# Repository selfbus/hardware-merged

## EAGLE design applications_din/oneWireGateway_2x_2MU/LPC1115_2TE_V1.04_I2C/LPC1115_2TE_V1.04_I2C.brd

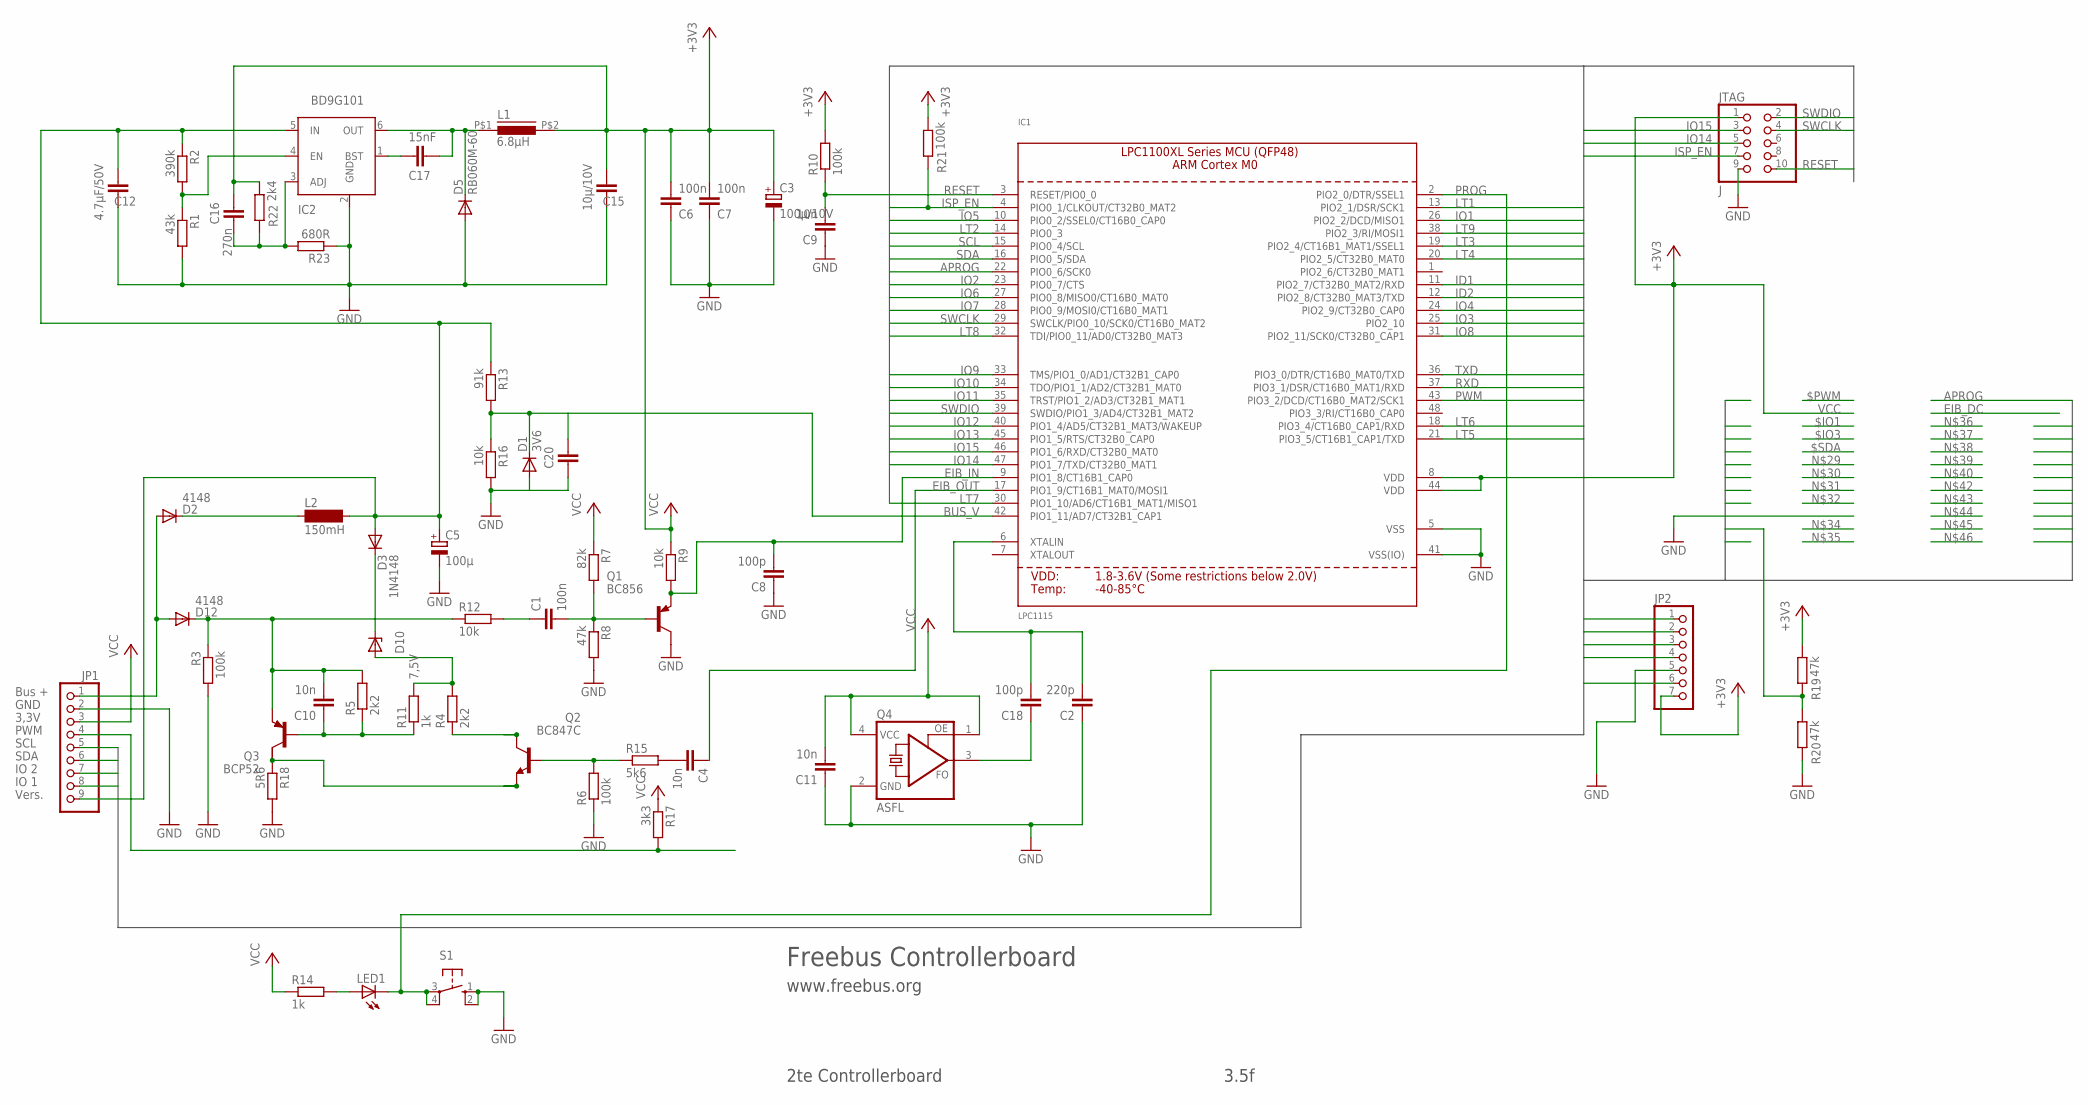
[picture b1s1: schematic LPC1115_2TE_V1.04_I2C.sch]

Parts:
C1, C6, C7: 100n; C1206
C2: 220p; C1206
C3: 100µ/10V; E2,5-5
C4, C10, C11: 10n; C1206
C5: 100µ; E3,5-8
C8: 100p; C1206K
C9: 10n; C1206K
C12: 4.7µF/50V; C1206K
C15: 10µ/10V; C1206K
C16: 270n; C1206
C17: 15nF; C1206
C18: 100p; C1206
C20: C-EUC1206; C1206
D1: 3V6; MINIMELF
D2, D12: 4148; MINIMELF
D3: 1N4148; MINIMELF
D5: RB060M-60; SOD123
D10: 7,5V; MINIMELF
IC1: LPC1115; LQFP48
IC2: BD9G101; SOT23-6
JP1: PINHD-1X9; 1X09
JP2: PINHD-1X7; 1X07
JTAG: J; 2X05M
L1: 6.8µH; PIS2812
L2: 150mH; BS11
LED1: LED3MM
Q1: BC856; SOT23-BEC
Q2: BC847C; SOT23
Q3: BCP52; SOT223
Q4: ASFL; ASF
R1: 43k; R1206
R2: 390k; R1206
R3, R6, R10, R21: 100k; R1206
R4, R5: 2k2; R1206
R7: 82k; R1206
R8, R19, R20: 47k; R1206
R9, R12, R16: 10k; R1206
R11, R14: 1k; R1206
R13: 91k; R1206
R15: 5k6; R1206
R17: 3k3; R1206
R18: 5R6; R1206
R22: 2k4; R1206
R23: 680R; R1206
S1: 10-XX; B3F-10XX

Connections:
APROG: IC1.22 (PIO0_6/SCK0), JP1.8
BASE: C1.2, Q1.B, R7.2, R8.1
BASE_SEND: Q2.1 (B), R6.2, R15.1
BUS_V: C20.2, D1.C, IC1.42 (PIO1_11/AD7/CT32B1_CAP1), R13.2, R16.1
EIB+: D2.A, D12.A, JP1.1
EIB_DC: C5.+, C12.2, D3.A, IC2.5 (IN), JP1.9, L2.2, R2.1, R13.1
EIB_IN: C8.2, IC1.9 (PIO1_8/CT16B1_CAP0), Q1.E, R9.2
EIB_OUT: C4.1, IC1.17 (PIO1_9/CT16B1_MAT0/MOSI1)
GND: C2.1, C3.-, C5.-, C6.1, C7.1, C8.1, C9.1, C11.1, C12.1, C15.1, C20.1, D1.A, D5.A, IC1.5 (VSS), IC1.41 (VSS(IO)), IC2.2 (GND), JP1.2, JP2.5, JTAG.9, Q1.C, Q4.2 (GND), R1.2, R3.2, R6.1, R8.2, R16.2, R18.2, R20.1, R23.1, S1.1 (S), S1.2 (S1)
ID1: IC1.11 (PIO2_7/CT32B0_MAT2/RXD)
ID2: IC1.12 (PIO2_8/CT32B0_MAT3/TXD)
IO1: IC1.26 (PIO2_2/DCD/MISO1)
IO2: IC1.23 (PIO0_7/CTS)
IO3: IC1.25 (PIO2_10)
IO4: IC1.24 (PIO2_9/CT32B0_CAP0)
IO5: IC1.10 (PIO0_2/SSEL0/CT16B0_CAP0)
IO6: IC1.27 (PIO0_8/MISO0/CT16B0_MAT0), JP1.7
IO7: IC1.28 (PIO0_9/MOSI0/CT16B0_MAT1)
IO8: IC1.31 (PIO2_11/SCK0/CT32B0_CAP1)
IO9: IC1.33 (TMS/PIO1_0/AD1/CT32B1_CAP0)
IO10: IC1.34 (TDO/PIO1_1/AD2/CT32B1_MAT0)
IO11: IC1.35 (TRST/PIO1_2/AD3/CT32B1_MAT1)
IO12: IC1.40 (PIO1_4/AD5/CT32B1_MAT3/WAKEUP), R19.1, R20.2
IO13: IC1.45 (PIO1_5/RTS/CT32B0_CAP0)
IO14: IC1.47 (PIO1_7/TXD/CT32B0_MAT1), JTAG.5
IO15: IC1.46 (PIO1_6/RXD/CT32B0_MAT0), JTAG.3
ISP_EN: IC1.4 (PIO0_1/CLKOUT/CT32B0_MAT2), JTAG.7, R21.1
I_SENSE: Q2.2 (E), Q3.2 (C), R18.1
LT1: IC1.13 (PIO2_1/DSR/SCK1), JP2.1
LT2: IC1.14 (PIO0_3)
LT3: IC1.19 (PIO2_4/CT16B1_MAT1/SSEL1), JP2.6
LT4: IC1.20 (PIO2_5/CT32B0_MAT0)
LT5: IC1.21 (PIO3_5/CT16B1_CAP1/TXD)
LT6: IC1.18 (PIO3_4/CT16B0_CAP1/RXD), JP2.2
LT7: IC1.30 (PIO1_10/AD6/CT16B1_MAT1/MISO1), JP2.3
LT8: IC1.32 (TDI/PIO0_11/AD0/CT32B0_MAT3)
LT9: IC1.38 (PIO2_3/RI/MOSI1), JP2.4
LX: C17.1, D5.C, IC2.6 (OUT), L1.P$1 (1)
unnamed: Q2.3 (C), R4.1
unnamed: C2.2, C18.2, IC1.6 (XTALIN)
unnamed: C10.2, D12.C, Q3.3 (E), R3.1, R5.2, R12.1
unnamed: C18.1, Q4.3 (FO)
unnamed: LED1.A, R14.2
unnamed: D2.C, L2.1
unnamed: D3.C, D10.C
unnamed: C1.1, R12.2
unnamed: C4.2, R15.2
unnamed: C17.2, IC2.1 (BST)
unnamed: IC2.4 (EN), R1.1, R2.2
unnamed: C16.1, IC2.3 (ADJ), R22.1, R23.2
unnamed: C10.1, Q3.1 (B), R5.1, R11.1
PROG: IC1.2 (PIO2_0/DTR/SSEL1), LED1.K (C), S1.3, S1.4 (P1)
PWM: IC1.43 (PIO3_2/DCD/CT16B0_MAT2/SCK1), JP1.4, R17.2
REFERENZ: D10.A, R4.2, R11.2
RESET: C9.2, IC1.3 (RESET/PIO0_0), JTAG.10, R10.1
RXD: IC1.37 (PIO3_1/DSR/CT16B0_MAT1/RXD)
SCL: IC1.15 (PIO0_4/SCL), JP1.5
SDA: IC1.16 (PIO0_5/SDA), JP1.6
SWCLK: IC1.29 (SWCLK/PIO0_10/SCK0/CT16B0_MAT2), JTAG.4
SWDIO: IC1.39 (SWDIO/PIO1_3/AD4/CT32B1_MAT2), JTAG.2
TXD: IC1.36 (PIO3_0/DTR/CT16B0_MAT0/TXD)
VCC: C3.+, C6.2, C7.2, C11.2, C15.2, C16.2, IC1.8 (VDD), IC1.44 (VDD), JP1.3, JP2.7, JTAG.1, L1.P$2 (2), Q4.1 (OE), Q4.4 (VCC), R7.1, R9.1, R10.2, R14.1, R17.1, R19.2, R21.2, R22.2

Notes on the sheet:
Bus +
GND
3,3V
PWM
IO 1
IO 2
SDA
SCL
Vers.
Freebus Controllerboard
www.freebus.org
2te Controllerboard
3.5f

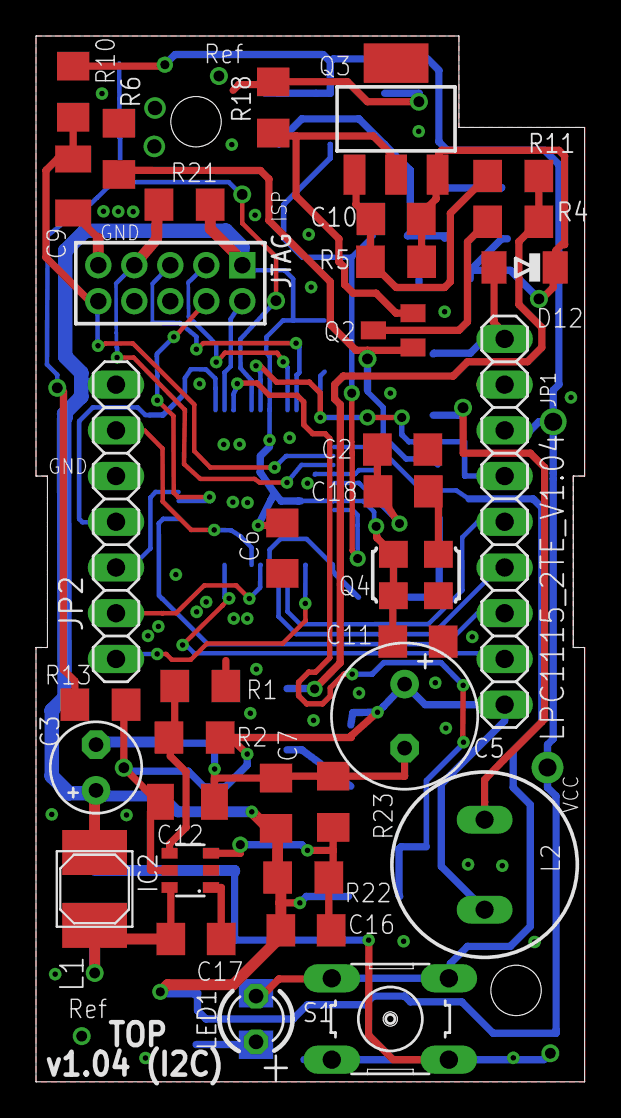
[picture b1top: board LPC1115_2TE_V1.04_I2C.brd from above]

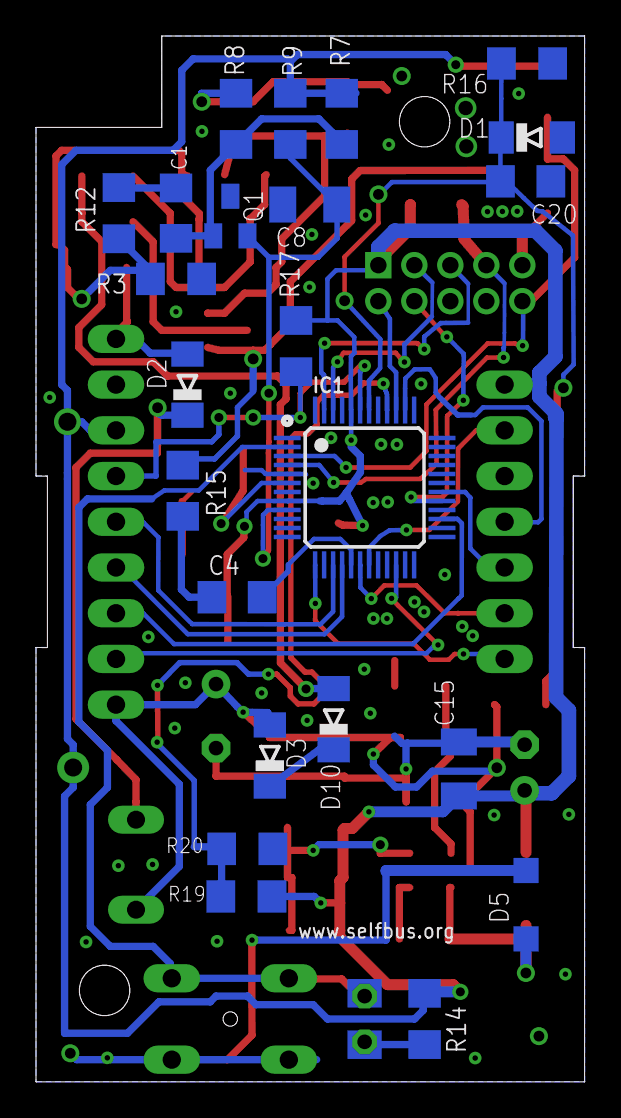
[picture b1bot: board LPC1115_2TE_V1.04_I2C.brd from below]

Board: 2 copper layers, 30.5 x 58.1 mm, 59 parts (23 on the bottom side), 43 nets.

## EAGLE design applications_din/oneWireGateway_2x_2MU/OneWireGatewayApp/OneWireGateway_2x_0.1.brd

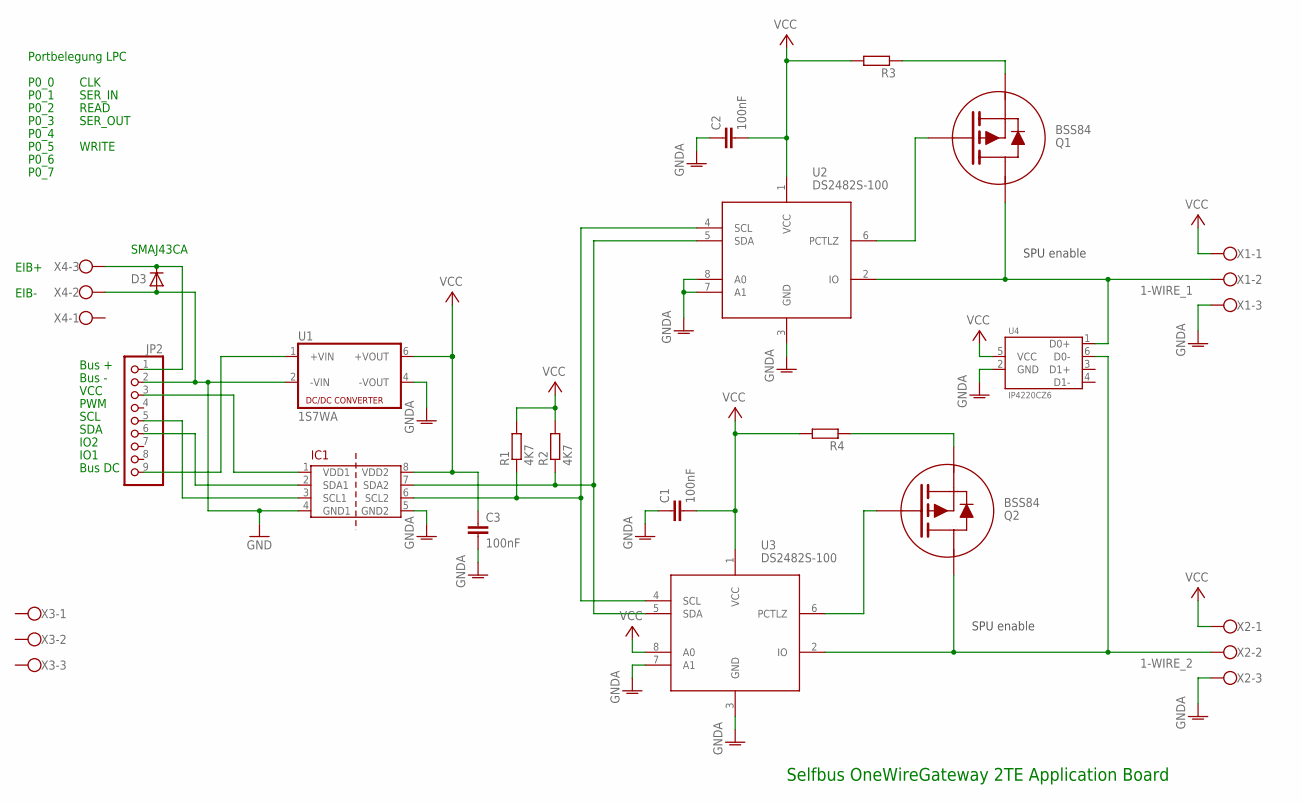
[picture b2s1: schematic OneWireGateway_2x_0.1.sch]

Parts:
C1, C2, C3: 100nF; C0805
D3: D-SMB; SMB
IC1: ADUM1250; SO08
JP2: PINHD-1X9; 1X09
Q1, Q2: BSS84; SOT-23-3
R1, R2: 4K7; R0805
R3, R4: R-EU_R0805; R0805
U1: 1S7WA; 7PIN_SIP
U2, U3: DS2482S-100; SO8
U4: IP4220CZ6; SOT-6
X1, X2: W237-03P; W237-133
X3, X4: W237-3E

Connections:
1-WIRE_1: Q1.3 (D), U2.2 (IO), U4.1 (D0+), X1.2
1-WIRE_2: Q2.3 (D), U3.2 (IO), U4.6 (D0-), X2.2
EIB+: D3.1 (C), JP2.1, X4.3
GND: D3.2 (A), IC1.4 (GND1), JP2.2, U1.2 (-VIN), X4.2
GNDA: C1.1, C2.1, C3.2, IC1.5 (GND2), U1.4 (-VOUT), U2.3 (GND), U2.7 (A1), U2.8 (A0), U3.3 (GND), U3.7 (A1), U4.2 (GND), X1.3, X2.3
unnamed: Q1.1 (G), U2.6 (PCTLZ)
unnamed: Q1.2 (S), R3.1
unnamed: JP2.9, U1.1 (+VIN)
unnamed: Q2.1 (G), U3.6 (PCTLZ)
unnamed: IC1.2 (SDA1), JP2.6
unnamed: IC1.3 (SCL1), JP2.5
unnamed: Q2.2 (S), R4.1
unnamed: IC1.1 (VDD1), JP2.3
SCL: IC1.6 (SCL2), R1.1, U2.4 (SCL), U3.4 (SCL)
SDA: IC1.7 (SDA2), R2.1, U2.5 (SDA), U3.5 (SDA)
VCC: C1.2, C2.2, C3.1, IC1.8 (VDD2), R1.2, R2.2, R3.2, R4.2, U1.6 (+VOUT), U2.1 (VCC), U3.1 (VCC), U3.8 (A0), U4.5 (VCC), X1.1, X2.1

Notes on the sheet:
Selfbus OneWireGateway 2TE Application Board
SMAJ43CA
Bus +
Bus -
VCC
PWM
IO1
IO2
SDA
SCL
EIB+
EIB-
SER_IN
CLK
READ
SER_OUT
WRITE
P0_0
P0_1
P0_2
P0_3
P0_4
P0_5
P0_6
P0_7
Portbelegung LPC
SPU enable
Bus DC

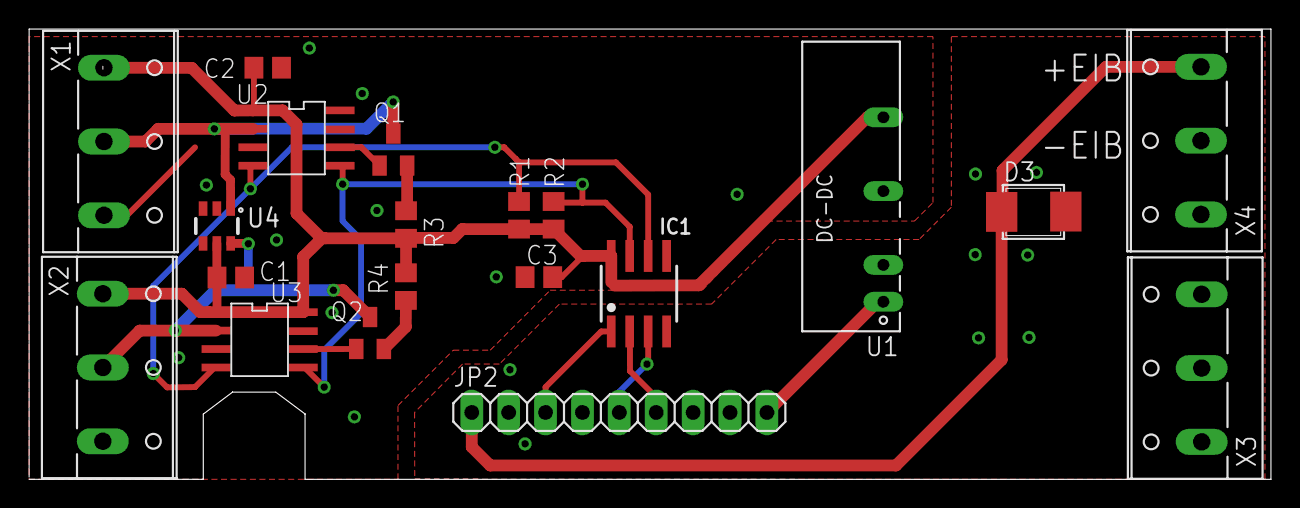
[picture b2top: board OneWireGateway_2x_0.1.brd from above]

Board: 2 copper layers, 85.5 x 31.0 mm, 20 parts (0 on the bottom side), 16 nets.

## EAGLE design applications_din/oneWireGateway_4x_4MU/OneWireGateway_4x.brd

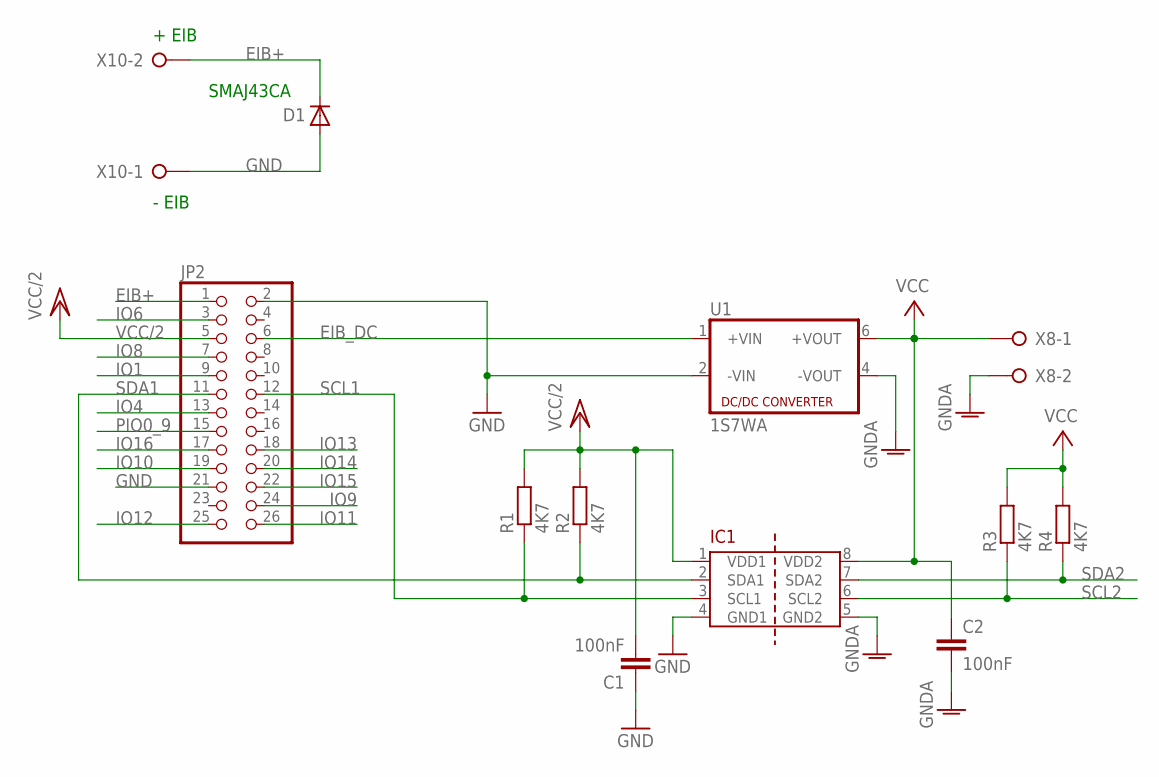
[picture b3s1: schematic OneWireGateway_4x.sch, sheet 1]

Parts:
C1, C2: 100nF; C0805
D1: SMAJ40CA; SMB
IC1: ADUM1250; SO08
JP2: PINHD-2X13_2.54-SMD; 2X13SMD
R1, R2, R3, R4: 4K7; R0805
U1: 1S7WA; 7PIN_SIP
X8, X10: W237-02P; W237-132

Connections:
EIB+: D1.1 (C), JP2.1, X10.2
EIB_DC: JP2.6, U1.1 (+VIN)
GND: C1.1, D1.2 (A), IC1.4 (GND1), JP2.2, JP2.21, U1.2 (-VIN), X10.1
GNDA: C2.2, IC1.5 (GND2), U1.4 (-VOUT), X8.2; also elsewhere on the board
IO1: JP2.9
IO4: JP2.13
IO6: JP2.3
IO8: JP2.7
IO9: JP2.24
IO10: JP2.19
IO11: JP2.26
IO12: JP2.25
IO13: JP2.18
IO14: JP2.20
IO15: JP2.22
IO16: JP2.17
PIO0_9: JP2.15
SCL1: IC1.3 (SCL1), JP2.12, R1.1
SCL2: IC1.6 (SCL2), R3.1; also elsewhere on the board
SDA1: IC1.2 (SDA1), JP2.11, R2.1
SDA2: IC1.7 (SDA2), R4.1; also elsewhere on the board
VCC: C2.1, IC1.8 (VDD2), R3.2, R4.2, U1.6 (+VOUT), X8.1; also elsewhere on the board
VCC/2: C1.2, IC1.1 (VDD1), JP2.5, R1.2, R2.2

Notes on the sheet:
+ EIB
- EIB
SMAJ43CA

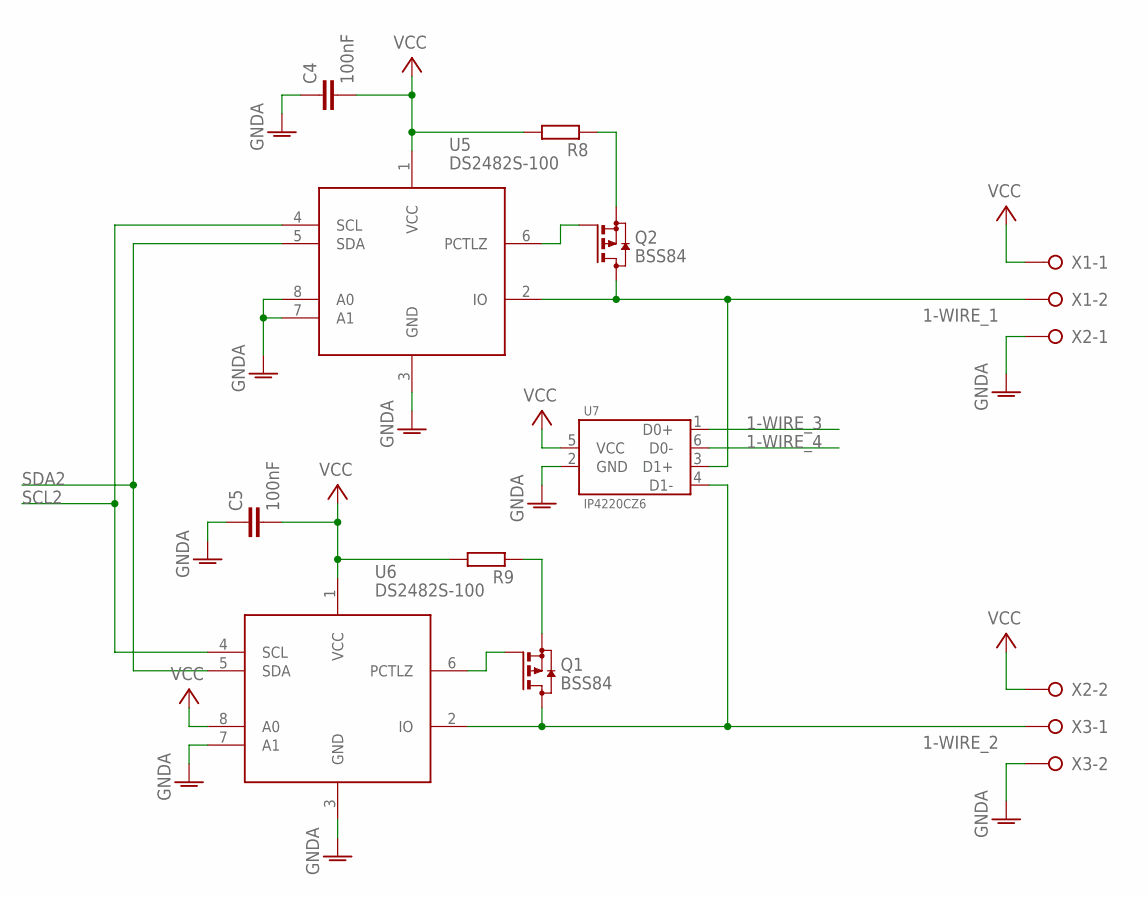
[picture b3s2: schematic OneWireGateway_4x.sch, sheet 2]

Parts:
C4, C5: 100nF; C0805
Q1, Q2: BSS84; SOT23
R8, R9: R-EU_R0805; R0805
U5, U6: DS2482S-100; SO8
U7: IP4220CZ6; SOT-6
X1, X2, X3: W237-02P; W237-132

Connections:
1-WIRE_1: Q2.3 (D), U5.2 (IO), U7.3 (D1+), X1.2
1-WIRE_2: Q1.3 (D), U6.2 (IO), U7.4 (D1-), X3.1
1-WIRE_3: U7.1 (D0+); also elsewhere on the board
1-WIRE_4: U7.6 (D0-); also elsewhere on the board
GNDA: C4.1, C5.1, U5.3 (GND), U5.7 (A1), U5.8 (A0), U6.3 (GND), U6.7 (A1), U7.2 (GND), X2.1, X3.2; also elsewhere on the board
unnamed: Q2.1 (G), U5.6 (PCTLZ)
unnamed: Q2.2 (S), R8.1
unnamed: Q1.2 (S), R9.1
unnamed: Q1.1 (G), U6.6 (PCTLZ)
SCL2: U5.4 (SCL), U6.4 (SCL); also elsewhere on the board
SDA2: U5.5 (SDA), U6.5 (SDA); also elsewhere on the board
VCC: C4.2, C5.2, R8.2, R9.2, U5.1 (VCC), U6.1 (VCC), U6.8 (A0), U7.5 (VCC), X1.1, X2.2; also elsewhere on the board

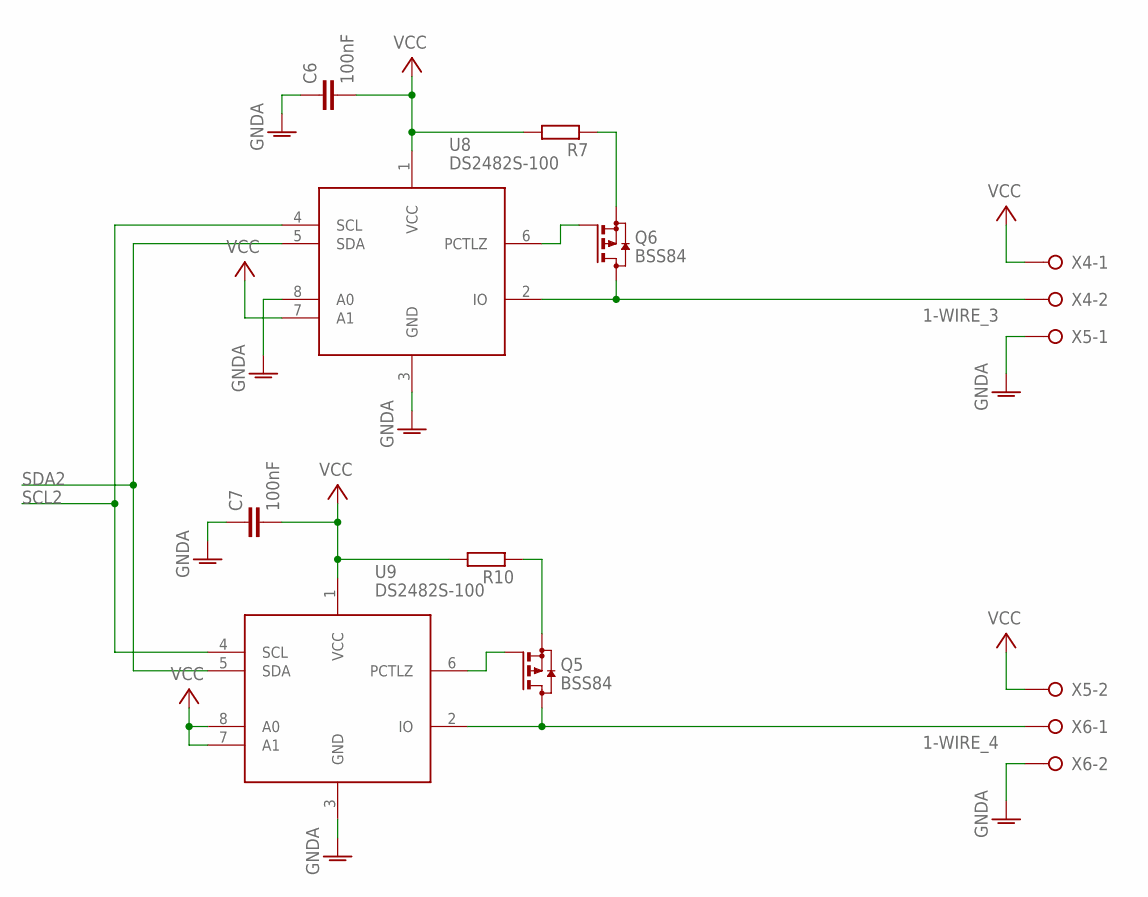
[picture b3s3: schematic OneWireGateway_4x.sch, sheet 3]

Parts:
C6, C7: 100nF; C0805
Q5, Q6: BSS84; SOT23
R7, R10: R-EU_R0805; R0805
U8, U9: DS2482S-100; SO8
X4, X5, X6: W237-02P; W237-132

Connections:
1-WIRE_3: Q6.3 (D), U8.2 (IO), X4.2; also elsewhere on the board
1-WIRE_4: Q5.3 (D), U9.2 (IO), X6.1; also elsewhere on the board
GNDA: C6.1, C7.1, U8.3 (GND), U8.8 (A0), U9.3 (GND), X5.1, X6.2; also elsewhere on the board
unnamed: Q6.1 (G), U8.6 (PCTLZ)
unnamed: Q6.2 (S), R7.1
unnamed: Q5.2 (S), R10.1
unnamed: Q5.1 (G), U9.6 (PCTLZ)
SCL2: U8.4 (SCL), U9.4 (SCL); also elsewhere on the board
SDA2: U8.5 (SDA), U9.5 (SDA); also elsewhere on the board
VCC: C6.2, C7.2, R7.2, R10.2, U8.1 (VCC), U8.7 (A1), U9.1 (VCC), U9.7 (A1), U9.8 (A0), X4.1, X5.2; also elsewhere on the board

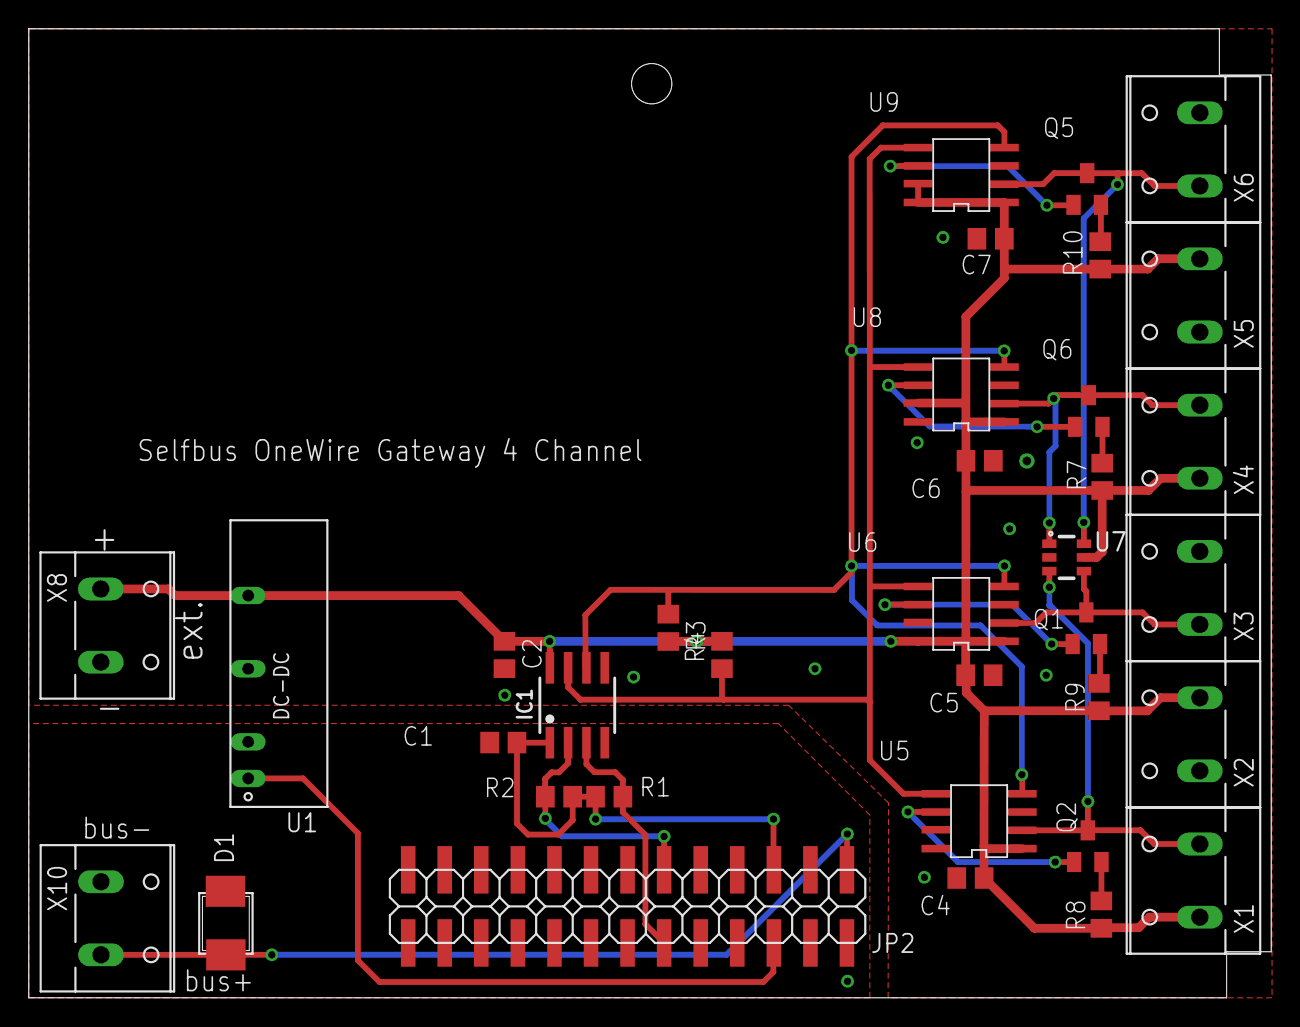
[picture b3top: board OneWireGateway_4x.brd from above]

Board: 2 copper layers, 86.3 x 67.3 mm, 35 parts (0 on the bottom side), 22 nets.

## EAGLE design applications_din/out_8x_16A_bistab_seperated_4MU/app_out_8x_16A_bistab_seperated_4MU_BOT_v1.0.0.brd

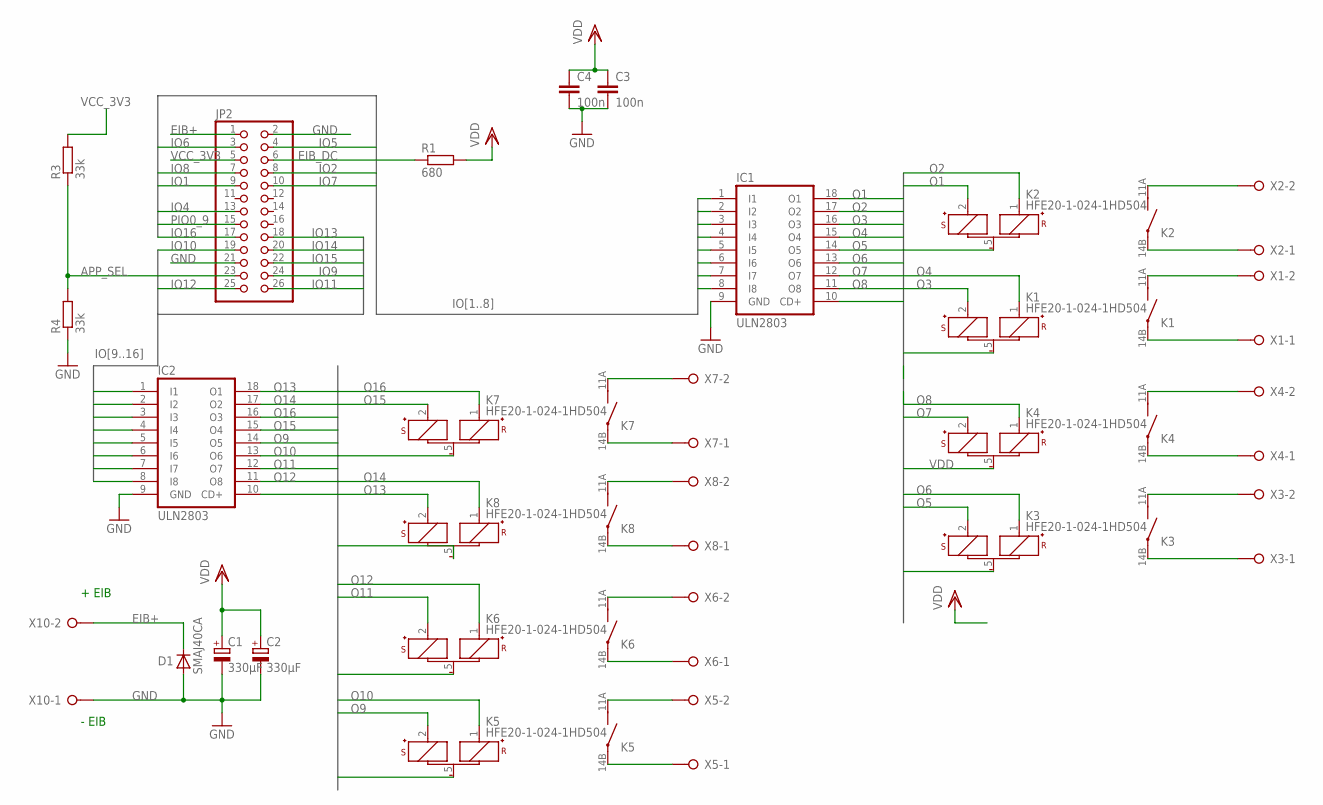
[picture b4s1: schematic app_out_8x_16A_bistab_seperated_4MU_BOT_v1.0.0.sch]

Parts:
C1, C2: 330µF; E3,5-8
C3, C4: 100n; C1206
D1: SMAJ40CA; SMB
IC1, IC2: ULN2803; SO18W
JP2: PINHD-2X13_2.54-SMD; 2X13SMD
K1, K2, K3, K4, K5, K6, K7, K8: HFE20-1-024-1HD504; HFE20-3-504
R1: 680; M1206
R3, R4: 33k; M1206
X1, X2, X3, X4, X5, X6, X7, X8, X10: W237-02P; W237-132

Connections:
APP_SEL: JP2.23, R3.1, R4.2
EIB+: D1.1 (C), JP2.1, X10.2
EIB_DC: JP2.6, R1.1
GND: C1.-, C2.-, C3.2, C4.2, D1.2 (A), IC1.9 (GND), IC2.9 (GND), JP2.2, JP2.21, R4.1, X10.1
IO1: IC1.5 (I5), JP2.9
IO2: IC1.4 (I4), JP2.8
IO4: IC1.8 (I8), JP2.13
IO5: IC1.1 (I1), JP2.4
IO6: IC1.2 (I2), JP2.3
IO7: IC1.6 (I6), JP2.10
IO8: IC1.3 (I3), JP2.7
IO9: IC2.5 (I5), JP2.24
IO10: IC2.6 (I6), JP2.19
IO11: IC2.7 (I7), JP2.26
IO12: IC2.8 (I8), JP2.25
IO13: IC2.1 (I1), JP2.18
IO14: IC2.2 (I2), JP2.20
IO15: IC2.4 (I4), JP2.22
IO16: IC2.3 (I3), JP2.17
K12: K2.14B (PA), X2.1
K34: K4.14B (PA), X4.1
K56: K6.11A (PB), X6.2
K78: K7.11A (PB), X7.2
unnamed: K4.11A (PB), X4.2
unnamed: K7.14B (PA), X7.1
unnamed: K1.14B (PA), X1.1
unnamed: K3.14B (PA), X3.1
unnamed: K8.14B (PA), X8.1
unnamed: K5.14B (PA), X5.1
unnamed: K1.11A (PB), X1.2
unnamed: K2.11A (PB), X2.2
unnamed: K3.11A (PB), X3.2
unnamed: K8.11A (PB), X8.2
unnamed: K5.11A (PB), X5.2
unnamed: K6.14B (PA), X6.1
O1: IC1.18 (O1), K2.2 (S+)
O2: IC1.17 (O2), K2.1 (R+)
O3: IC1.16 (O3), K1.2 (S+)
O4: IC1.15 (O4), K1.1 (R+)
O5: IC1.14 (O5), K3.2 (S+)
O6: IC1.13 (O6), K3.1 (R+)
O7: IC1.12 (O7), K4.2 (S+)
O8: IC1.11 (O8), K4.1 (R+)
O9: IC2.14 (O5), K5.2 (S+)
O10: IC2.13 (O6), K5.1 (R+)
O11: IC2.12 (O7), K6.2 (S+)
O12: IC2.11 (O8), K6.1 (R+)
O13: IC2.18 (O1), K8.2 (S+)
O14: IC2.17 (O2), K8.1 (R+)
O15: IC2.15 (O4), K7.2 (S+)
O16: IC2.16 (O3), K7.1 (R+)
PIO0_9: IC1.7 (I7), JP2.15
VCC_3V3: JP2.5, R3.2
VDD: C1.+, C2.+, C3.1, C4.1, IC1.10 (CD+), IC2.10 (CD+), K1.5 (-), K2.5 (-), K3.5 (-), K4.5 (-), K5.5 (-), K6.5 (-), K7.5 (-), K8.5 (-), R1.2

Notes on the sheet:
+ EIB
- EIB

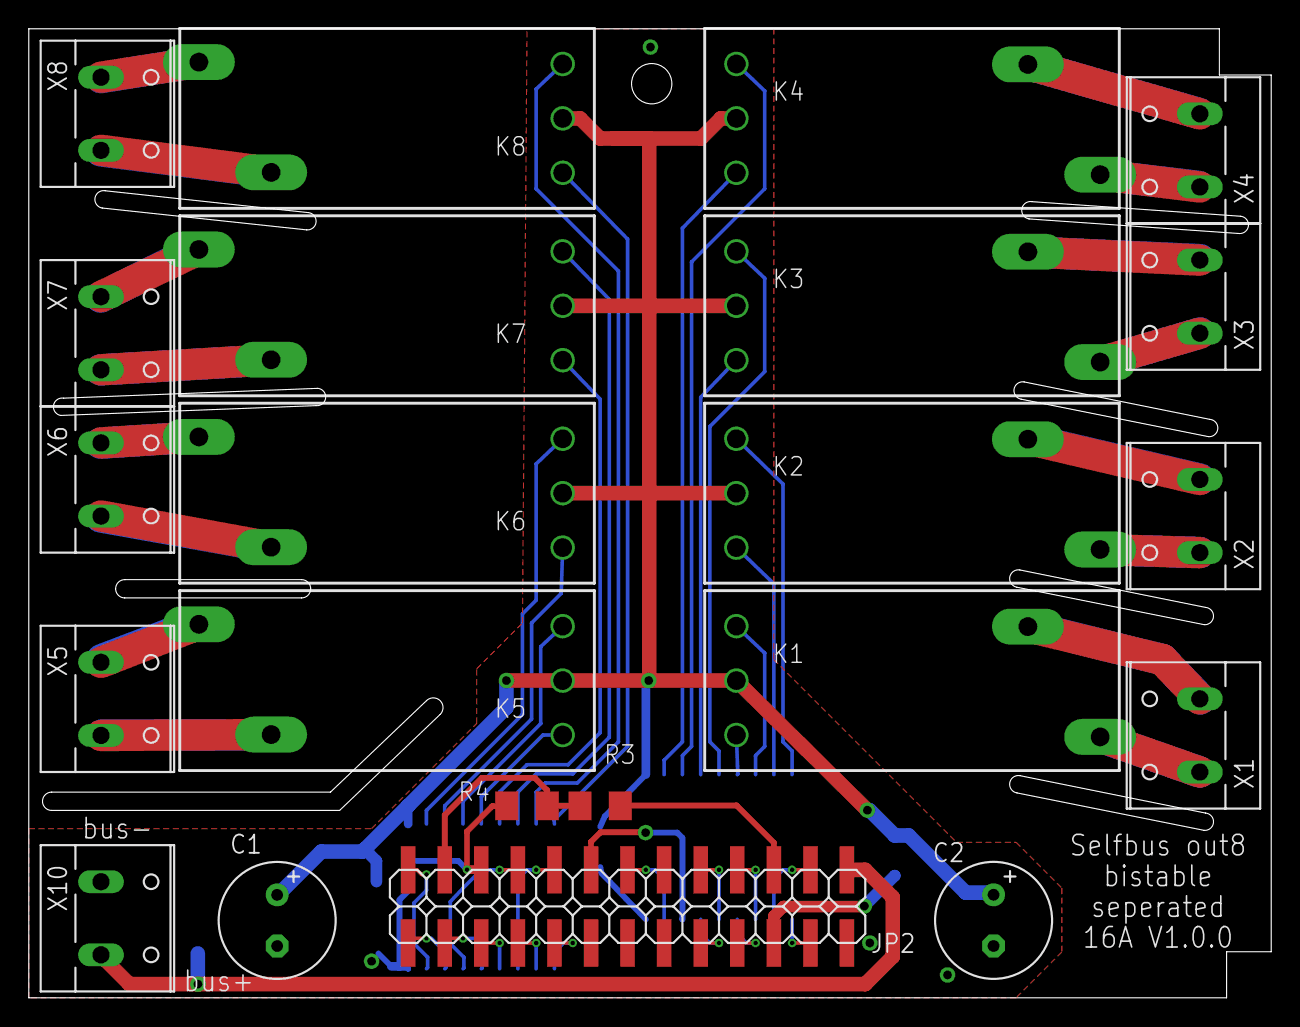
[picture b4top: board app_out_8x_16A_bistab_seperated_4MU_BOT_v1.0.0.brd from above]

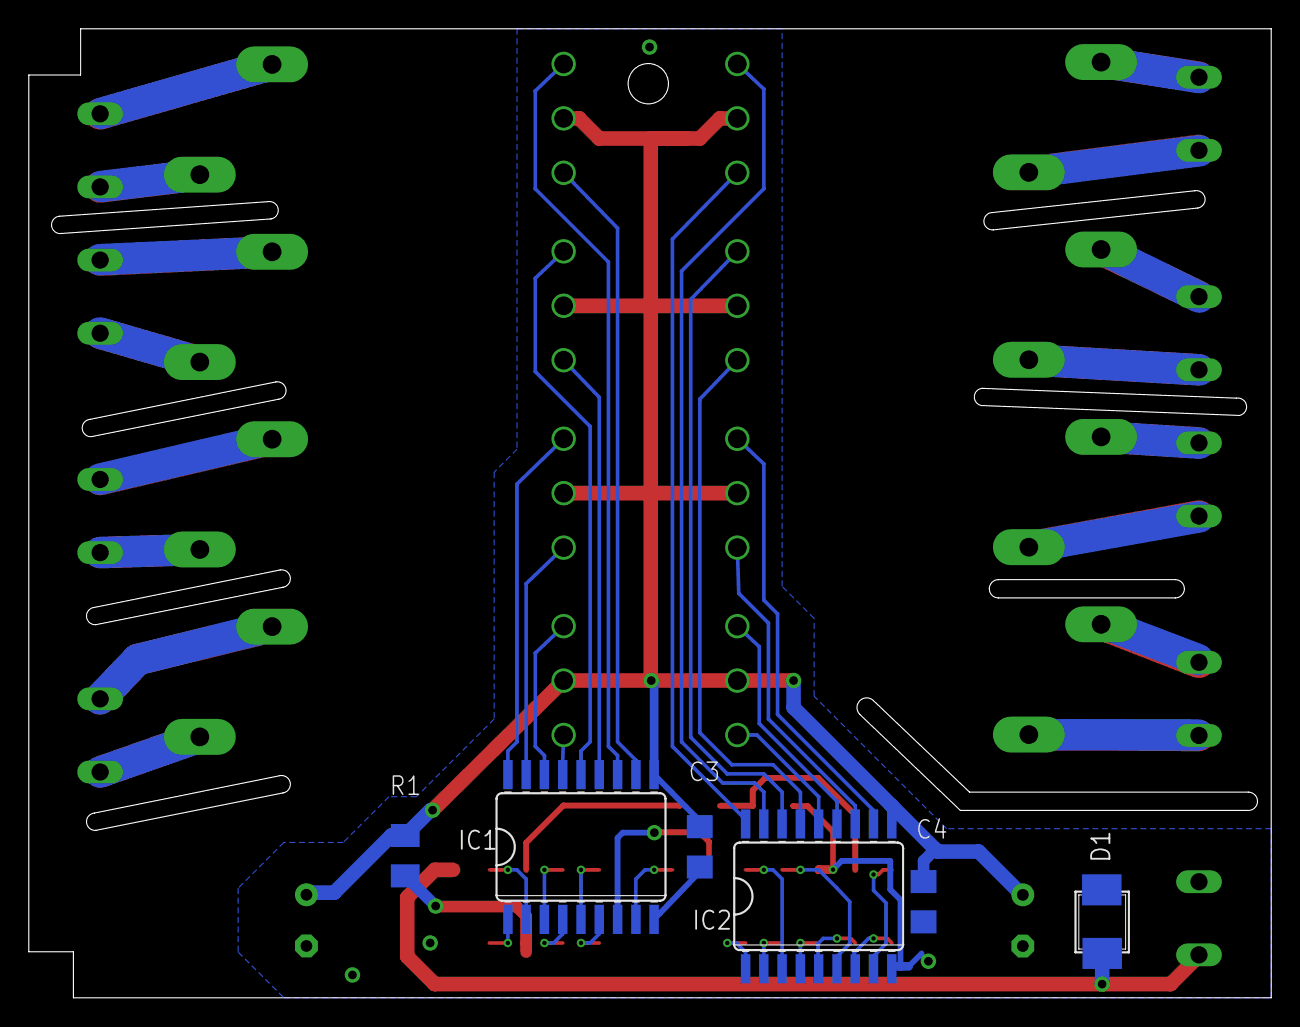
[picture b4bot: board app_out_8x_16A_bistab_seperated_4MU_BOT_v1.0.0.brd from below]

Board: 2 copper layers, 86.3 x 67.3 mm, 28 parts (6 on the bottom side), 54 nets.

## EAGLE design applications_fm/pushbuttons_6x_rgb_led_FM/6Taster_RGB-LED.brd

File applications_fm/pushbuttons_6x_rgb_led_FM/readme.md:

This hardware component is used to build a 6x push button sensor with LEDs and proximity sensor: </br>
https://selfbus.org/wiki/devices/inputs/63-push-button-sensor-6x-with-rgb-leds-and-proximity-sensor

<hr>
Du hast Ideen, wie man diese Komponente weiterentwickeln oder in anderen Geräten einsetzen könnte? Lass es uns wissen und werde Teil unserer Community!
Do you have ideas on how to further develop this component or how to use it in other devices? Let us know and become part of our community!
<br />--> https://selfbus.org
<br />--> https://selfbus.org/forum
<br />--> https://selfbus.org/chat

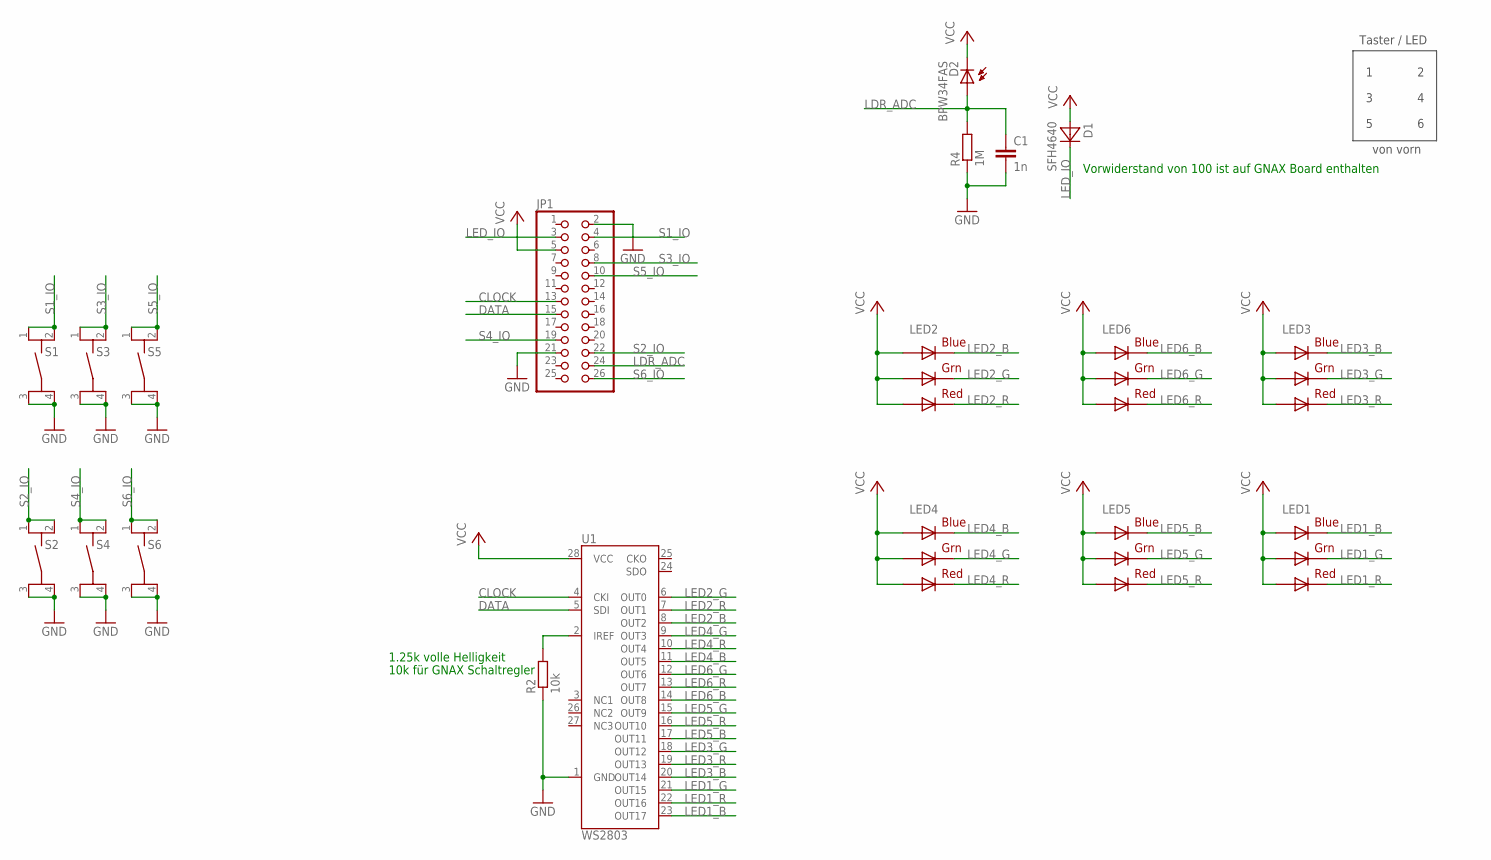
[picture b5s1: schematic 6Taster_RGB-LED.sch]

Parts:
C1: 1n; C0805
D1: SFH4640
D2: BPW34FAS
JP1: PINHD-2X13_2.54-SMD; 2X13SMD
LED1, LED2, LED3, LED4, LED5, LED6: RGB; RGBLED5050
R2: 10k; R0805
R4: 1M; R0805
S1, S2, S3, S4, S5, S6: TASTER_9314SMD; TASTER_9314
U1: WS2803; SOP-28

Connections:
CLOCK: JP1.13, U1.4 (CKI)
DATA: JP1.15, U1.5 (SDI)
GND: C1.2, JP1.2, JP1.21, R2.1, R4.1, S1.3, S1.4, S2.3, S2.4, S3.3, S3.4, S4.3, S4.4, S5.3, S5.4, S6.3, S6.4, U1.1 (GND)
LDR_ADC: C1.1, D2.ANODE (A), JP1.24, R4.2
LED1_B: LED1.4 (BLUE_C), U1.23 (OUT17)
LED1_G: LED1.6 (GREEN_C), U1.21 (OUT15)
LED1_R: LED1.5 (RED_C), U1.22 (OUT16)
LED2_B: LED2.4 (BLUE_C), U1.8 (OUT2)
LED2_G: LED2.6 (GREEN_C), U1.6 (OUT0)
LED2_R: LED2.5 (RED_C), U1.7 (OUT1)
LED3_B: LED3.4 (BLUE_C), U1.20 (OUT14)
LED3_G: LED3.6 (GREEN_C), U1.18 (OUT12)
LED3_R: LED3.5 (RED_C), U1.19 (OUT13)
LED4_B: LED4.4 (BLUE_C), U1.11 (OUT5)
LED4_G: LED4.6 (GREEN_C), U1.9 (OUT3)
LED4_R: LED4.5 (RED_C), U1.10 (OUT4)
LED5_B: LED5.4 (BLUE_C), U1.17 (OUT11)
LED5_G: LED5.6 (GREEN_C), U1.15 (OUT9)
LED5_R: LED5.5 (RED_C), U1.16 (OUT10)
LED6_B: LED6.4 (BLUE_C), U1.14 (OUT8)
LED6_G: LED6.6 (GREEN_C), U1.12 (OUT6)
LED6_R: LED6.5 (RED_C), U1.13 (OUT7)
LED_IO: D1.KATHODE (C), JP1.3
unnamed: R2.2, U1.2 (IREF)
S1_IO: JP1.4, S1.1, S1.2
S2_IO: JP1.22, S2.1, S2.2
S3_IO: JP1.8, S3.1, S3.2
S4_IO: JP1.19, S4.1, S4.2
S5_IO: JP1.10, S5.1, S5.2
S6_IO: JP1.26, S6.1, S6.2
VCC: D1.ANODE (A), D2.KATHODE (C), JP1.5, LED1.1 (GREEN_A), LED1.2 (RED_A), LED1.3 (BLUE_A), LED2.1 (GREEN_A), LED2.2 (RED_A), LED2.3 (BLUE_A), LED3.1 (GREEN_A), LED3.2 (RED_A), LED3.3 (BLUE_A), LED4.1 (GREEN_A), LED4.2 (RED_A), LED4.3 (BLUE_A), LED5.1 (GREEN_A), LED5.2 (RED_A), LED5.3 (BLUE_A), LED6.1 (GREEN_A), LED6.2 (RED_A), LED6.3 (BLUE_A), U1.28 (VCC)

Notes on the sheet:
Taster / LED
von vorn
Vorwiderstand von 100 ist auf GNAX Board enthalten
1.25k volle Helligkeit
10k für GNAX Schaltregler

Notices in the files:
parts and their libraries:
microbuilder: This work is placed in the public domain, and may be freely used for commercial and non-commercial work with the following conditions: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
